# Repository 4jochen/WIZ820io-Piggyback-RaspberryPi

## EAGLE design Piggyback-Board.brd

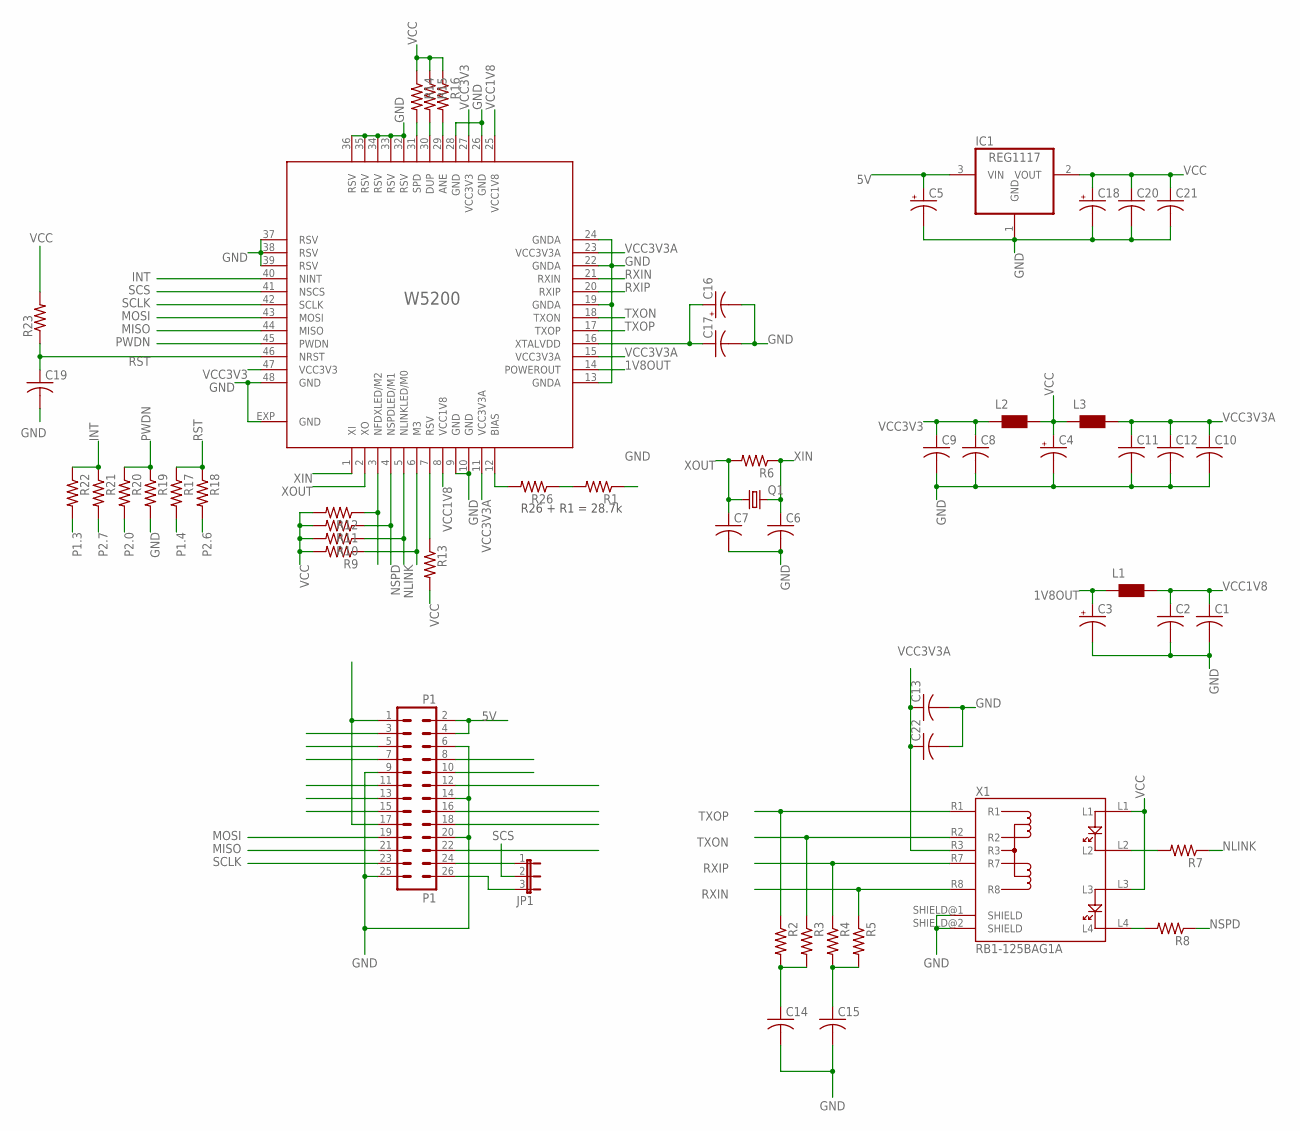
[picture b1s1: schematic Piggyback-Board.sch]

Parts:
C1, C2, C6, C7, C8, C9, C10, C11, C12, C13, C14, C15, C17, C19, C20, C21, C22: C-USC0603; C0603
C3, C4, C16: CPOL-USA/3216-18R; A/3216-18R
C5, C18: CPOL-USB/3528-21R; B/3528-21R
IC1: REG1117; SOT223
JP1: JP2E; JP2
L1, L2, L3: WE-CBF_0603; 0603
P1: P1; MA13-2
Q1: CRYSTALSM49; SM49
R1, R2, R3, R4, R5, R6, R7, R8, R9, R10, R11, R12, R13, R14, R15, R16, R17, R18, R19, R20, R21, R22, R23, R26: R-US_R0603; R0603
W5200: W5200; QFN48
X1: RB1-125BAG1A

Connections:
1V8OUT: C3.+, L1.1, W5200.14 (POWEROUT)
5V: C5.+, IC1.3 (VIN), P1.2, P1.4
BIAS: R26.2, W5200.12 (BIAS)
GND: C1.2, C2.2, C3.-, C4.-, C5.-, C6.2, C7.2, C8.2, C9.2, C10.2, C11.2, C12.2, C13.2, C14.2, C15.2, C16.-, C17.2, C18.-, C19.2, C20.2, C21.2, C22.2, IC1.1 (GND), P1.6, P1.9, P1.14, P1.20, P1.25, R1.1, R19.2, W5200.9 (GND), W5200.10 (GND), W5200.13 (GNDA), W5200.19 (GNDA), W5200.22 (GNDA), W5200.24 (GNDA), W5200.26 (GND), W5200.28 (GND), W5200.32 (RSV), W5200.33 (RSV), W5200.34 (RSV), W5200.35 (RSV), W5200.36 (RSV), W5200.37 (RSV), W5200.38 (RSV), W5200.39 (RSV), W5200.48 (GND), W5200.EXP (GND), X1.SHIELD@1 (SHIELD), X1.SHIELD@2 (SHIELD)
INT: R21.1, R22.1, W5200.40 (NINT)
M2: R12.1, W5200.3 (NFDXLED/M2)
M3: R9.1, W5200.6 (M3)
MISO: P1.21, W5200.44 (MISO)
MOSI: P1.19, W5200.43 (MOSI)
unnamed: JP1.1, P1.24
unnamed: JP1.3, P1.26
unnamed: P1.1, P1.17
unnamed: R1.2, R26.1
unnamed: R7.2, X1.L2
unnamed: R8.2, X1.L4
unnamed: R14.2, W5200.31 (SPD)
unnamed: R15.2, W5200.30 (DUP)
unnamed: C14.1, R2.2, R3.2
unnamed: C15.1, R4.2, R5.2
unnamed: R16.2, W5200.29 (ANE)
NLINK: R7.1, R10.1, W5200.5 (NLINKLED/M0)
NSPD: R8.1, R11.1, W5200.4 (NSPDLED/M1)
P1.3: R22.2
P1.4: R17.2
P2.0: R20.2
P2.6: R18.2
P2.7: R21.2
PWDN: R19.1, R20.1, W5200.45 (PWDN)
RST: C19.1, R17.1, R18.1, R23.1, W5200.46 (NRST)
RSV: R13.1, W5200.7 (RSV)
RXIN: R5.1, W5200.21 (RXIN), X1.R8
RXIP: R4.1, W5200.20 (RXIP), X1.R7
SCLK: P1.23, W5200.42 (SCLK)
SCS: JP1.2, W5200.41 (NSCS)
TXON: R3.1, W5200.18 (TXON), X1.R2
TXOP: R2.1, W5200.17 (TXOP), X1.R1
VCC: C4.+, C18.+, C20.1, C21.1, IC1.2 (VOUT), L2.2, L3.1, R9.2, R10.2, R11.2, R12.2, R13.2, R14.1, R15.1, R16.1, R23.2, X1.L1, X1.L3
VCC1V8: C1.1, C2.1, L1.2, W5200.8 (VCC1V8), W5200.25 (VCC1V8)
VCC3V3: C8.1, C9.1, L2.1, W5200.27 (VCC3V3), W5200.47 (VCC3V3)
VCC3V3A: C10.1, C11.1, C12.1, C13.1, C22.1, L3.2, W5200.11 (VCC3V3A), W5200.15 (VCC3V3A), W5200.23 (VCC3V3A), X1.R3
XIN: C6.1, Q1.2, R6.1, W5200.1 (XI)
XOUT: C7.1, Q1.1, R6.2, W5200.2 (XO)
XTALVDD: C16.+, C17.1, W5200.16 (XTALVDD)

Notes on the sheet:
R26 + R1 = 28.7k

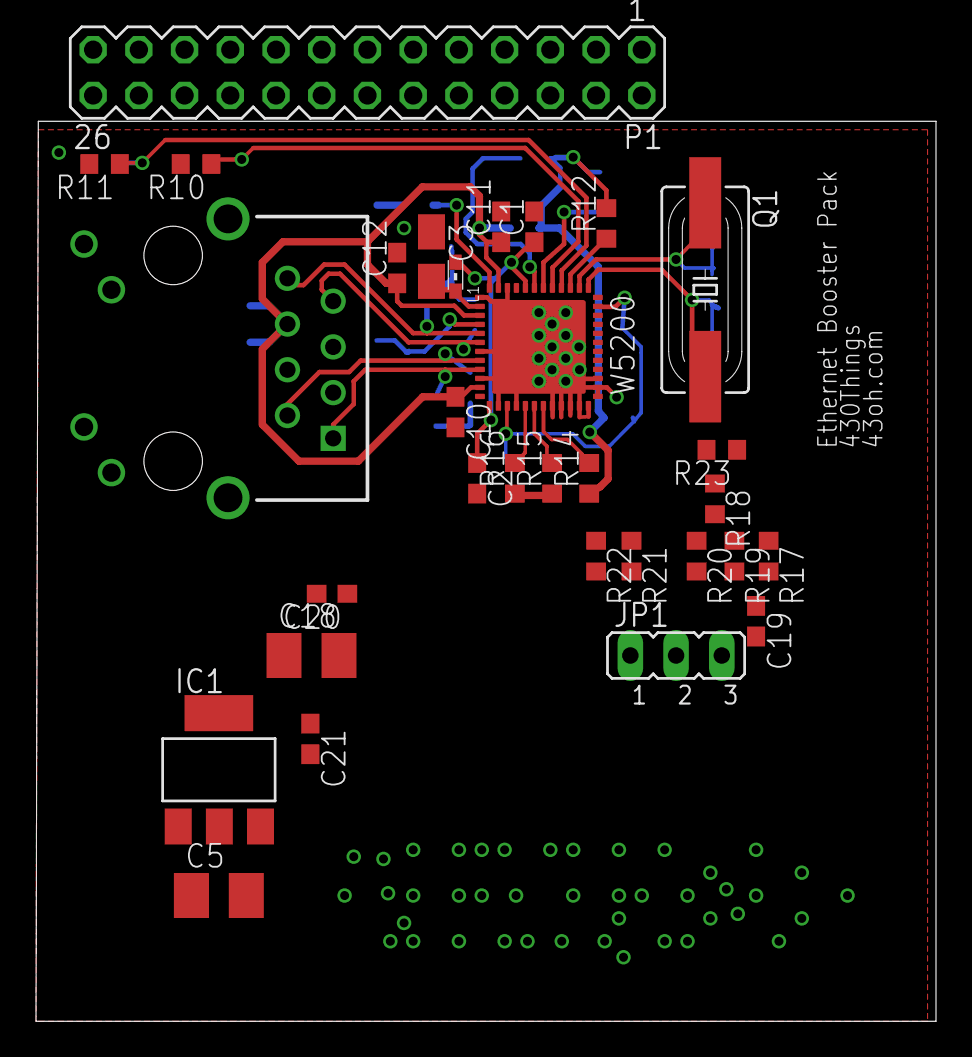
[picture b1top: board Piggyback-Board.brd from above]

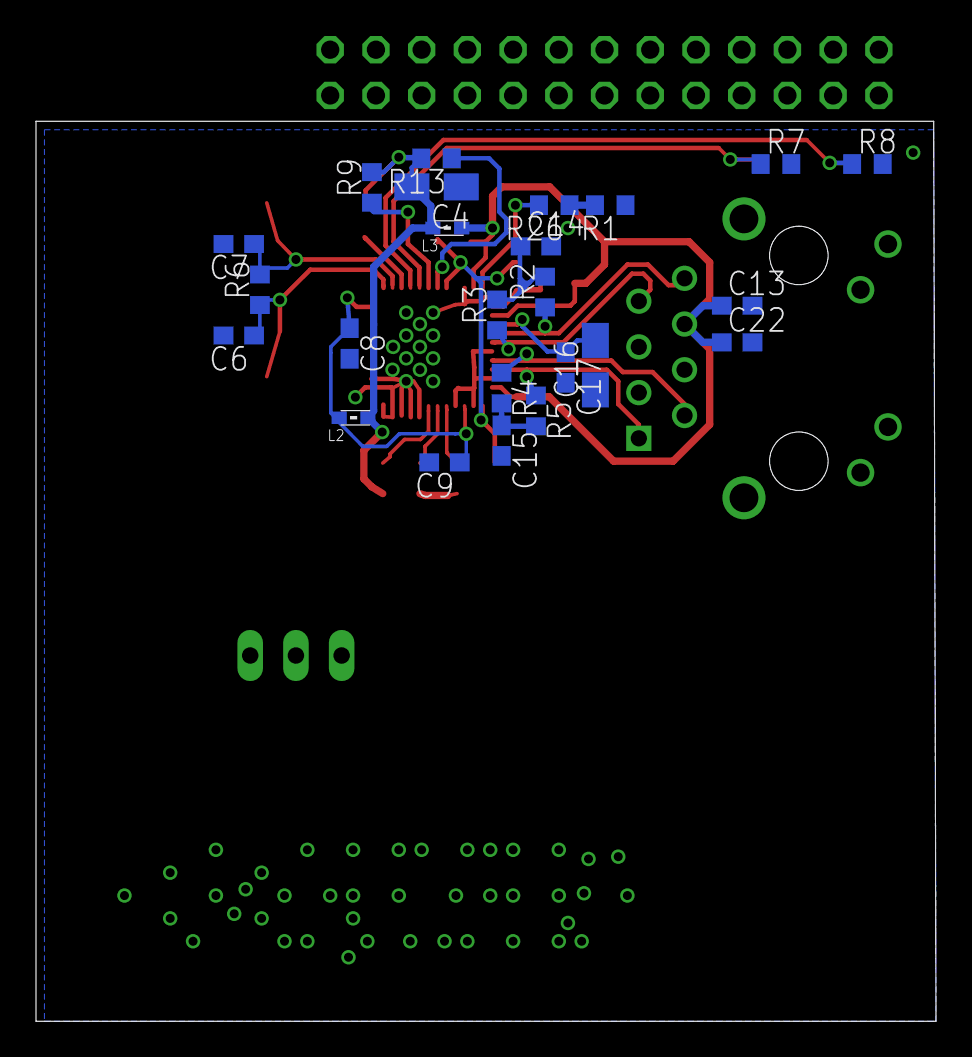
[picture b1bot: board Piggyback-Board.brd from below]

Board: 2 copper layers, 50.0 x 50.0 mm, 55 parts (24 on the bottom side), 38 nets.

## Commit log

2012-08-09 WIZnet WIZ820io Piggyback on Raspberry Pi initial version Eagle 6.1.0 light
